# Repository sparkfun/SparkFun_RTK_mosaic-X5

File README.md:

SparkFun RTK mosaic-X5
========================================

[*SparkFun RTK mosaic-X5 (SXM-E)*](https://www.sparkpnt.com/products/sparkpnt-sxm-e-cors)

Designed and manufactured in Boulder, Colorado, USA, the SparkFun RTK mosaic-X5 is the perfect solution for your high-precision positioning and navigation needs. Based around the multi-constellation, multi-frequency, L5-ready mosaic-X5 from Septentrio, this is our most advanced RTK product to date. It supports GNSS signals from GPS (USA), GLONASS (Russia), Beidou (China), Galileo (Europe), Navic (India) plus special additional satellites (e.g. SBAS and QZSS). The mosaic-X5 also has built-in on-module support for other L-band correction services.

The RTK mosaic-X5 can be configured as a Real Time Kinematic (RTK) Base, where it feeds corrections to other RTK Rovers, or as an RTK Rover where it can use corrections to achieve a horizontal positioning accuracy of 6 millimeters (0.6cm) (plus 0.5 PPM). For applications like robotics and autonomous systems, the mosaic-X5 can deliver position updates at 100Hz (100 times per second). The mosaic-X5 is a _very_ sophisticated chip running a full internal web page server; the position can be monitored and the module fully configured through that web page using a standard browser.

Under the hood, the RTK mosaic-X5 is based on the mosaic-X5 GNSS module from Septentrio, plus the Espressif ESP32-WROVER processor (16MB flash, 8MB PSRAM). The mosaic-X5 has USB-C connectivity (with Ethernet-over-USB), multiple UARTs and supports full Ethernet connectivity. The only interface it doesn't offer is WiFi and that's why we've included the ESP32 with its own Ethernet connection. You can connect the mosaic-X5 directly to your Ethernet network - our product supports Power-over-Ethernet too. Or you can link the mosaic-X5 Ethernet port to the ESP32 Ethernet port and have the ESP32 provide WiFi connectivity. In that mode, the ESP32 becomes an Ethernet to WiFi Bridge, seamlessly passing WiFi traffic to and from the mosaic-X5 via Ethernet.

Documentation
--------------

* **[Product Manual](http://docs.sparkfun.com/SparkFun_RTK_mosaic-X5/)** - Product manual for the RTK mosaic-X5 hosted by GitHub pages.<br>

*Need to download or print our hookup guide?*

* [Print *(Print to PDF)* from Single-Page View](http://docs.sparkfun.com/SparkFun_RTK_mosaic-X5/print_view)

Repository Contents
-------------------

* **[/docs](/docs/)** - Online documentation files
    * [assets](/docs/assets/) - Assets files
        * [board_files](/docs/assets/board_files/) - Files for the product design
            * [Schematic](/docs/assets/board_files/schematic.pdf) (.pdf)
            * [Dimensions](/docs/assets/board_files/dimensions.png) (.png)
            * [Eagle files](/docs/assets/board_files/eagle_files.zip) (.zip)
        * [img/hookup_guide/](/docs/assets/img/hookup_guide/) - Images for hookup guide documentation
* **[/Hardware](/Hardware/)** - Eagle design files (.brd, .sch)
* **[/Production](/Production/)** - PCB panel production files
* **[/Extruded_Case](/Extruded_Case/)** - Drawings and STEP file for the extruded case
* **[/Front_Panel](/Front_Panel/)** - Drawings and STEP file. Eagle design files (.brd, .sch) for the prototype (PCB) enclosure panel used to validate the dimensions
* **[/Rear_Panel](/Rear_Panel/)** - Drawings and STEP file. Eagle design files (.brd, .sch) for the prototype (PCB) enclosure panel used to validate the dimensions
* **[/Front_Sticker](/Front_Sticker/)** - DXF and PDF files for the front sticker
* **[/Rear_Sticker](/Rear_Sticker/)** - DXF and PDF files for the rear sticker
* **[/Firmware](/Firmware/)** - ESP IDF source code and binaries for the firmware which runs on the ESP32-WROVER
* **[/Test_Sketches](/Test_Sketches/)** - Additional code used to validate and test the RTK mosaic-X5
* **[/Documents](/Documents/)** - Component datasheets etc.

Product Variants
----------------

* [SXM-E](https://www.sparkpnt.com/products/sparkpnt-sxm-e-cors)- v1.0, Initial Release

Version History
---------------

* [v10](https://github.com/sparkfun/SparkFun_RTK_mosaic-X5/releases/tag/v10) - Initial Release

License Information
-------------------

This product is ***open source***!

Please review the [LICENSE.md](./LICENSE.md) file for license information.

If you have any questions or concerns about licensing, please contact technical support on our [SparkFun forums](https://community.sparkfun.com/).

Distributed as-is; no warranty is given.

- Your friends at SparkFun.

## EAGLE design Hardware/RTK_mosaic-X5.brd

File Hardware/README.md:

SparkFun RTK mosaic-X5 Design Files
=====================================

The .sch and .brd files here are Eagle CAD schematic and PCB design files from SparkFun Electronics.
A freeware version of Autodesk Eagle can be found [here](https://www.autodesk.com/products/eagle/free-download).

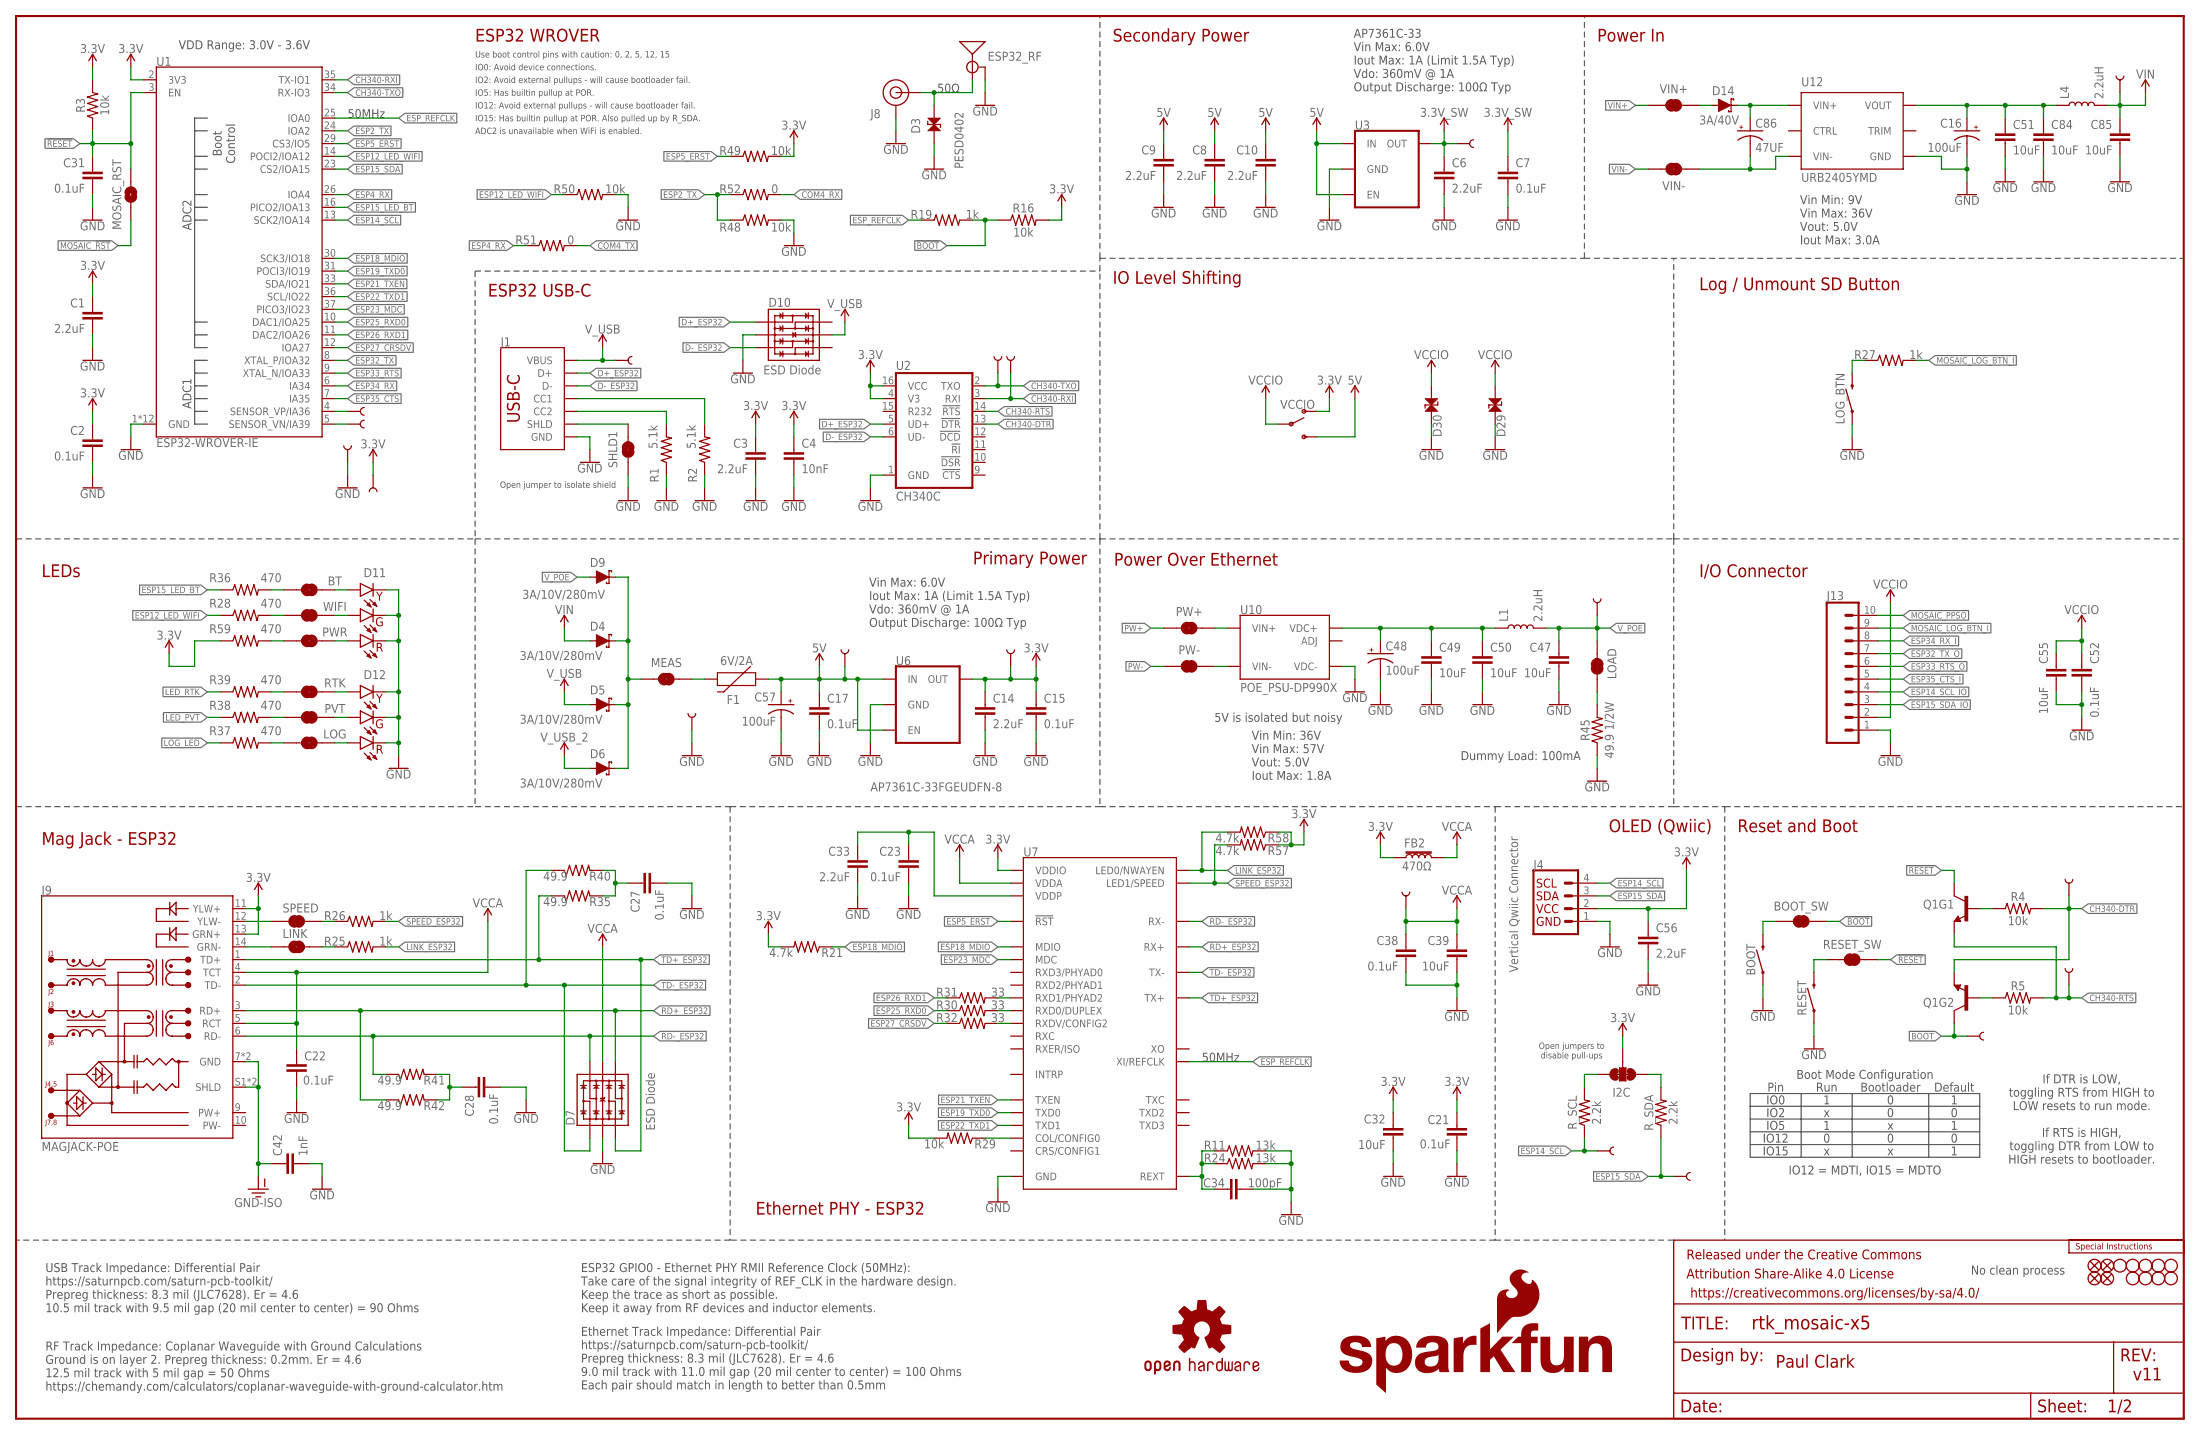
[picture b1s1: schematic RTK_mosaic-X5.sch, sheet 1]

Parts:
3V3, 3V3_SW, 5V: TEST-POINTPOGO_PTH; 1X01_NO_SILK
BOOT: MOMENTARY-SWITCH-SPST-PTH-RIGHT-ANGLE-8-020; TACTILE_SWITCH_PTH_RA_8-020
BOOT_SW: JUMPER-SMT_2_NC_TRACE_SILK; SMT-JUMPER_2_NC_TRACE_SILK
BT: JUMPER-SMT_2_NC_TRACE_SILK; SMT-JUMPER_2_NC_TRACE_SILK
C1, C3, C6, C8, C9, C10, C14, C33, C56: 2.2uF; 0603
C2, C7, C15, C17, C21, C22, C23, C27, C28, C31, C38, C52: 0.1uF; 0603
C4: 10nF; 0603
C16, C48, C57: 100uF; PANASONIC_D
C32, C39, C55: 10uF; 0603
C34: 100pF; 0603
C42: 1nF; 1206
C47, C49, C50, C51, C84, C85: 10uF; 0805
C86: 47UF; PANASONIC_D
D3, D29, D30: PESD0402; 0402
D4, D5, D6, D9: 3A/10V/280mV; SOD-323
D7, D10: ESD Diode; SOT-23-6
D11, D12: Yellow Green Red; CBI_LED_T-3MM_PTH
D14: 3A/40V; SMA-DIODE
DTR: TEST-POINTPOGO_PTH; 1X01_NO_SILK
ESP1, ESP2, ESP36, ESP39: TEST-POINTPOGO_PTH; 1X01_NO_SILK
ESP32_RF: ANTENNA-SMA-GROUNDEDEDGE_RPSMA; RP-SMA-EDGE
F1: 6V/2A; 1210
FB2: 470Ω; 0603
FD1, FD2, FD3, FD4: FIDUCIAL1X2; FIDUCIAL-1X2
FRAME1: FRAME-LEDGER; CREATIVE_COMMONS
GND: TEST-POINTPOGO_PTH; 1X01_NO_SILK
H1, H2, H3, H4, H5, H6, H7, H8, H10: STAND-OFFTIGHT; STAND-OFF-TIGHT
I2C: JUMPER-SMT_3_2-NC_TRACE_SILK; SMT-JUMPER_3_2-NC_TRACE_SILK
J1: USB_C_4-LAYER_PADS; USB-C-16P_4LAYER-PADS
J4: Vertical Qwiic Connector; JST04_1MM_VERT
J8: U.FL2PIN-REDUCED-FOOTPRINT; U.FL_REDUCED_FOOTPRINT
J9: MAGJACK-POE; MAGJACK-SYM_LED
J13: CONN_10_3.5MM_RA_HEADER; 1X10_SCREW_TERMINAL_3.5MM
L1, L4: 2.2uH; 0805-WIDE
LINK: JUMPER-SMT_2_NC_TRACE_SILK; SMT-JUMPER_2_NC_TRACE_SILK
LOAD: JUMPER-SMT_2_NC_TRACE_SILK; SMT-JUMPER_2_NC_TRACE_SILK
LOG: JUMPER-SMT_2_NC_TRACE_SILK; SMT-JUMPER_2_NC_TRACE_SILK
LOGO1: SPECIAL_INSTRUCTIONS-ORDERING; ORDERING_INSTRUCTIONS
LOGO4: OSHW-LOGOS; OSHW-LOGO-S
LOGO5: SFE_LOGO_NAME.2_INCH; SFE_LOGO_NAME_.2
LOGO6: SFE_LOGO_FLAME.2_INCH; SFE_LOGO_FLAME_.2
LOG_BTN: MOMENTARY-SWITCH-SPST-PTH-RIGHT-ANGLE-8-020; TACTILE_SWITCH_PTH_RA_8-020
MEAS: JUMPER-COMBO_2_NC_TRACE; COMBO-JUMPER_2_NC_TRACE
MOSAIC_RST: JUMPER-COMBO_2_NO; COMBO-JUMPER_2_NO
PVT: JUMPER-SMT_2_NC_TRACE_SILK; SMT-JUMPER_2_NC_TRACE_SILK
PW+: JUMPER-COMBO_2_NC_TRACE; COMBO-JUMPER_2_NC_TRACE
PW-: JUMPER-COMBO_2_NC_TRACE; COMBO-JUMPER_2_NC_TRACE
PWR: JUMPER-SMT_2_NC_TRACE_SILK; SMT-JUMPER_2_NC_TRACE_SILK
Q1: TRANS_NPN_DUAL-MBT3904DW1T1; SC70-6
R1, R2: 5.1k; 0603
R3, R4, R5, R16, R29, R48, R49, R50: 10k; 0603
R11, R24: 13k; 0603
R19, R25, R26, R27: 1k; 0603
R21, R57, R58: 4.7k; 0603
R28, R36, R37, R38, R39, R59: 470; 0603
R30, R31, R32: 33; 0603
R35, R40, R41, R42: 49.9; 0603
R45: 49.9 1/2W; 1206
R51, R52: 0; 0603
RESET: MOMENTARY-SWITCH-SPST-PTH-RIGHT-ANGLE-8-020; TACTILE_SWITCH_PTH_RA_8-020
RESET_SW: JUMPER-SMT_2_NC_TRACE_SILK; SMT-JUMPER_2_NC_TRACE_SILK
RTK: JUMPER-SMT_2_NC_TRACE_SILK; SMT-JUMPER_2_NC_TRACE_SILK
RTS: TEST-POINTPOGO_PTH; 1X01_NO_SILK
RX: TEST-POINTPOGO_PTH; 1X01_NO_SILK
R_SCL: 2.2k; 0603
R_SDA: 2.2k; 0603
SCL2: TEST-POINTPOGO_PTH; 1X01_NO_SILK
SDA2: TEST-POINTPOGO_PTH; 1X01_NO_SILK
SHLD1: JUMPER-SMT_2_NC_TRACE_SILK; SMT-JUMPER_2_NC_TRACE_SILK
SPEED: JUMPER-SMT_2_NC_TRACE_SILK; SMT-JUMPER_2_NC_TRACE_SILK
TP_BOOT: TEST-POINTPOGO_PTH; 1X01_NO_SILK
TX: TEST-POINTPOGO_PTH; 1X01_NO_SILK
U1: ESP32-WROVER-IE; ESP32-WROVER-E/IE
U2: CH340C; SO016
U3, U6: AP7361C-33FGEUDFN-8; UDFN-8
U7: KSZ8041NLI; MLF55Q-32LD
U10: POE_PSU-DP990X; DP990X
U12: URB2405YMD; URB_YMD-15WR3
VCCA: TEST-POINTPOGO_PTH; 1X01_NO_SILK
VCCIO: SWITCH-SPDT-SMD-AYZ0202; SWITCH_DPDT_SMD_AYZ0202
VIN: TEST-POINTPOGO_PTH; 1X01_NO_SILK
VIN+: JUMPER-COMBO_2_NC_TRACE; COMBO-JUMPER_2_NC_TRACE
VIN-: JUMPER-COMBO_2_NC_TRACE; COMBO-JUMPER_2_NC_TRACE
VPOE: TEST-POINTPOGO_PTH; 1X01_NO_SILK
VUSB: TEST-POINTPOGO_PTH; 1X01_NO_SILK
WIFI: JUMPER-SMT_2_NC_TRACE_SILK; SMT-JUMPER_2_NC_TRACE_SILK

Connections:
3.3V: 3V3.1, C1.1, C2.1, C3.1, C4.1, C14.1, C15.1, C21.1, C32.1, C56.1, ESP2.1, FB2.1, I2C.2, J4.2, J9.11 (YLW+), J9.13 (GRN+), R3.2, R16.2, R21.2, R29.2, R49.2, R57.1, R58.1, R59.1, U1.2 (3V3), U2.4 (V3), U2.16 (VCC), U6.1 (OUT), U7.17 (VDDIO), VCCIO.1 (O); also elsewhere on the board
3.3V_SW: 3V3_SW.1, C6.1, C7.1, U3.1 (OUT); also elsewhere on the board
5V: 5V.1, C8.1, C9.1, C10.1, C17.1, C57.+, F1.1, U3.5 (EN), U3.8 (IN), U6.5 (EN), U6.8 (IN), VCCIO.3 (S); also elsewhere on the board
5V_RAW: C48.+, C49.1, C50.1, L1.1, U10.1 (VDC+), U10.2 (VDC+)
5V_RAW1: C16.+, C51.1, C84.1, L4.1, U12.4 (VOUT)
!BOOT!: BOOT_SW.1, Q1.6 (C), R16.1, R19.2, TP_BOOT.1
!RESET!: C31.1, MOSAIC_RST.2, MOSAIC_RST.4 (2), Q1.3 (C), R3.1, RESET_SW.1, U1.3 (EN)
CH340-DTR: DTR.1, Q1.1 (E), R4.2, U2.13 (!DTR)
CH340-RTS: Q1.4 (E), R5.2, RTS.1, U2.14 (!RTS)
CH340-RXI: TX.1, U1.35 (TX-IO1), U2.3 (RXI)
CH340-TXO: RX.1, U1.34 (RX-IO3), U2.2 (TXO)
COM4_RX: R52.2; also elsewhere on the board
COM4_TX: R51.2; also elsewhere on the board
D+_ESP32: D10.1 (IO1), J1.A6 (D+), J1.B6 (D+), U2.5 (UD+)
D-_ESP32: D10.3 (IO2), J1.A7 (D-), J1.B7 (D-), U2.6 (UD-)
ESP2_TX: R48.1, R52.1, U1.24 (IOA2)
ESP4_RX: R51.1, U1.26 (IOA4)
ESP5_ERST: R49.1, U1.29 (CS3/IO5), U7.32 (!RST!)
ESP12_LED_WIFI: R28.1, R50.1, U1.14 (POCI2/IOA12)
ESP14_SCL: J4.4, R_SCL.1, SCL2.1, U1.13 (SCK2/IOA14); also elsewhere on the board
ESP14_SCL_IO: J13.4; also elsewhere on the board
ESP15_LED_BT: R36.1, U1.16 (PICO2/IOA13)
ESP15_SDA: J4.3, R_SDA.1, SDA2.1, U1.23 (CS2/IOA15); also elsewhere on the board
ESP15_SDA_IO: J13.3; also elsewhere on the board
ESP18_MDIO: R21.1, U1.30 (SCK3/IO18), U7.11 (MDIO)
ESP19_TXD0: U1.31 (POCI3/IO19), U7.24 (TXD0)
ESP21_TXEN: U1.33 (SDA/IO21), U7.23 (TXEN)
ESP22_TXD1: U1.36 (SCL/IO22), U7.25 (TXD1)
ESP23_MDC: U1.37 (PICO3/IO23), U7.12 (MDC)
ESP25_RXD0: R30.1, U1.10 (DAC1/IOA25)
ESP26_RXD1: R31.1, U1.11 (DAC2/IOA26)
ESP27_CRSDV: R32.1, U1.12 (IOA27)
ESP32_RF: D3.1, ESP32_RF.SIG (SIGNAL), J8.FEED (SIGNAL)
ESP32_TX: U1.8 (XTAL_P/IOA32); also elsewhere on the board
ESP32_TX_O: J13.7; also elsewhere on the board
ESP33_RTS: U1.9 (XTAL_N/IOA33); also elsewhere on the board
ESP33_RTS_O: J13.6; also elsewhere on the board
ESP34_RX: U1.6 (IA34); also elsewhere on the board
ESP34_RX_I: J13.8; also elsewhere on the board
ESP35_CTS: U1.7 (IA35); also elsewhere on the board
ESP35_CTS_I: J13.5; also elsewhere on the board
ESP36: ESP36.1, U1.4 (SENSOR_VP/IA36)
ESP39: ESP39.1, U1.5 (SENSOR_VN/IA39)
ESP_REFCLK: R19.1, U1.25 (IOA0), U7.9 (XI/REFCLK)
GND: BOOT.1, C1.2, C2.2, C3.2, C4.2, C6.2, C7.2, C8.2, C9.2, C10.2, C14.2, C15.2, C16.-, C17.2, C21.2, C22.2, C23.2, C27.2, C28.2, C31.2, C32.2, C33.2, C34.2, C38.2, C39.2, C42.2, C47.2, C48.-, C49.2, C50.2, C51.2, C52.2, C55.2, C56.2, C57.-, C84.2, C85.2, D3.2, D7.2 (VSS), D10.2 (VSS), D11.CATHODE_1 (YELLOW_CATHODE), D11.CATHODE_2 (GREEN_CATHODE), D11.CATHODE_3 (RED_CATHODE), D12.CATHODE_1 (YELLOW_CATHODE), D12.CATHODE_2 (GREEN_CATHODE), D12.CATHODE_3 (RED_CATHODE), D29.2, D30.2, ESP1.1, ESP32_RF.GND@0 (GND), ESP32_RF.GND@1 (GND), ESP32_RF.GND@2 (GND), ESP32_RF.GND@3 (GND), GND.1, J1.GND, J1.GND2 (GND), J4.1, J8.1 (GND), J8.2 (GND), J13.1, LOG_BTN.1, R1.1, R2.1, R11.2, R24.2, R45.1, R48.2, R50.2, RESET.1, SHLD1.1, U1.1 (GND), U1.15 (GND), U1.38 (GND), U1.GND, U1.GNDT1 (GND), U1.GNDT2 (GND), U1.GNDT3 (GND), U1.GNDT4 (GND), U1.GNDT5 (GND), U1.GNDT6 (GND), U1.GNDT7 (GND), U1.GNDT8 (GND), U2.1 (GND), U3.4 (GND), U3.EP (GND), U6.4 (GND), U6.EP (GND), U7.1 (GND), U7.GND, U10.3 (VDC-), U12.6 (GND); also elsewhere on the board
GND-ISO: C42.1, J9.7 (GND), J9.8 (GND), J9.S1 (SHLD), J9.S2 (SHLD); also elsewhere on the board
LED_PVT: R38.1; also elsewhere on the board
LED_RTK: R39.1; also elsewhere on the board
LINK_ESP32: R25.2, R58.2, U7.30 (LED0/NWAYEN)
LOG_LED: R37.1; also elsewhere on the board
MEAS: D4.C, D5.C, D6.C, D9.C, MEAS.2, MEAS.4 (2)
MOSAIC_!RST!: MOSAIC_RST.1, MOSAIC_RST.3 (1); also elsewhere on the board
MOSAIC_LOG_BTN_I: J13.9, R27.2; also elsewhere on the board
MOSAIC_PPSO: J13.10; also elsewhere on the board
unnamed: J1.B5 (CC2), R1.2
unnamed: J1.A5 (CC1), R2.2
unnamed: J9.14 (GRN-), LINK.1
unnamed: Q1.2 (B), R5.1
unnamed: Q1.5 (B), R4.1
unnamed: J9.12 (YLW-), SPEED.1
unnamed: F1.2, MEAS.1, MEAS.3 (1)
unnamed: LOG_BTN.2, R27.1
unnamed: R26.1, SPEED.2
unnamed: I2C.3, R_SCL.2
unnamed: I2C.1, R_SDA.2
unnamed: LOG.2, R37.2
unnamed: D12.ANODE_3 (RED_ANODE), LOG.1
unnamed: D11.ANODE_2 (GREEN_ANODE), WIFI.1
unnamed: C27.1, R35.2, R40.2
unnamed: C28.1, R41.2, R42.2
unnamed: LINK.2, R25.1
unnamed: BT.1, D11.ANODE_1 (YELLOW_ANODE)
unnamed: C23.1, C33.1, U7.2 (VDDP)
unnamed: C34.1, R11.1, R24.1, U7.10 (REXT)
unnamed: R29.1, U7.28 (COL/CONFIG0)
unnamed: BT.2, R36.2
unnamed: LOAD.1, R45.2
unnamed: RESET.2, RESET_SW.2
unnamed: BOOT.2, BOOT_SW.2
unnamed: R30.2, U7.16 (RXD0/DUPLEX)
unnamed: R31.2, U7.15 (RXD1/PHYAD2)
unnamed: R28.2, WIFI.2
unnamed: D12.ANODE_2 (GREEN_ANODE), PVT.1
unnamed: D12.ANODE_1 (YELLOW_ANODE), RTK.1
unnamed: R39.2, RTK.2
unnamed: PVT.2, R38.2
unnamed: R32.2, U7.18 (RXDV/CONFIG2)
unnamed: PWR.2, R59.2
unnamed: D11.ANODE_3 (RED_ANODE), PWR.1
PW1+: PW+.1, PW+.3 (1), U10.5 (VIN+), U10.6 (VIN+)
PW1-: PW-.1, PW-.3 (1), U10.7 (VIN-), U10.8 (VIN-)
PW+: PW+.2, PW+.4 (2); also elsewhere on the board
PW-: PW-.2, PW-.4 (2); also elsewhere on the board
RD+_ESP32: D7.4 (IO3), J9.3 (RD+), R42.1, U7.5 (RX+)
RD-_ESP32: D7.6 (IO4), J9.6 (RD-), R41.1, U7.4 (RX-)
SHIELD: J1.SHLD1 (SHLD), J1.SHLD2 (SHLD), J1.SHLD3 (SHLD), J1.SHLD4 (SHLD), SHLD1.2
SPEED_ESP32: R26.2, R57.2, U7.31 (LED1/SPEED)
TD+_ESP32: D7.3 (IO2), J9.1 (TD+), R35.1, U7.7 (TX+)
TD-_ESP32: D7.1 (IO1), J9.2 (TD-), R40.1, U7.6 (TX-)
VCCA: C22.1, C38.1, C39.1, D7.5 (VCC), FB2.2, J9.4 (TCT), J9.5 (RCT), U7.3 (VDDA), VCCA.1
VCCIO: C52.1, C55.1, D29.1, D30.1, J13.2, VCCIO.2; also elsewhere on the board
VIN: C85.1, D4.A, L4.2, VIN.1
VIN1+: D14.A, VIN+.1, VIN+.3 (1)
VIN1-: C86.-, U12.2 (VIN-), VIN-.2, VIN-.4 (2)
VIN2+: C86.+, D14.C, U12.3 (VIN+)
VIN+: VIN+.2, VIN+.4 (2); also elsewhere on the board
VIN-: VIN-.1, VIN-.3 (1); also elsewhere on the board
V_POE: C47.1, D9.A, L1.2, LOAD.2, VPOE.1
V_USB: D5.A, D10.5 (VCC), J1.VBUS1 (VBUS), J1.VBUS2 (VBUS), VUSB.1
V_USB_2: D6.A; also elsewhere on the board

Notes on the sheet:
ESP32 WROVER
ESP32 USB-C
Paul Clark
v11
Reset and Boot
Secondary Power
Primary Power
Ethernet PHY - ESP32
Mag Jack - ESP32
VDD Range: 3.0V - 3.6V
If DTR is LOW, toggling RTS from HIGH to LOW resets to run mode. If RTS is HIGH, toggling DTR from LOW to HIGH resets to bootloader.
Pin
IO0
IO2
IO12
IO15
IO5
Run
Bootloader
Default
IO12 = MDTI, IO15 = MDTO
Boot Mode Configuration
IO0: Avoid device connections.
ADC2 is unavailable when WiFi is enabled.
IO12: Avoid external pullups - will cause bootloader fail.
Use boot control pins with caution: 0, 2, 5, 12, 15
IO2: Avoid external pullups - will cause bootloader fail.
IO15: Has builtin pullup at POR. Also pulled up by R_SDA.
IO5: Has builtin pullup at POR.
Open jumpers to disable pull-ups
Open jumper to isolate shield
AP7361C-33 Vin Max: 6.0V Iout Max: 1A (Limit 1.5A Typ) Vdo: 360mV @ 1A Output Discharge: 100Ω Typ
RF Track Impedance: Coplanar Waveguide with Ground Calculations Ground is on layer 2. Prepreg thickness: 0.2mm. Er = 4.6 12.5 mil track with 5 mil gap = 50 Ohms https://chemandy.com/calculators/coplanar-waveguide-with-ground-calculator.htm
USB Track Impedance: Differential Pair https://saturnpcb.com/saturn-pcb-toolkit/ Prepreg thickness: 8.3 mil (JLC7628). Er = 4.6 10.5 mil track with 9.5 mil gap (20 mil center to center) = 90 Ohms
50Ω
Power Over Ethernet
5V is isolated but noisy
Dummy Load: 100mA
Power In
OLED (Qwiic)

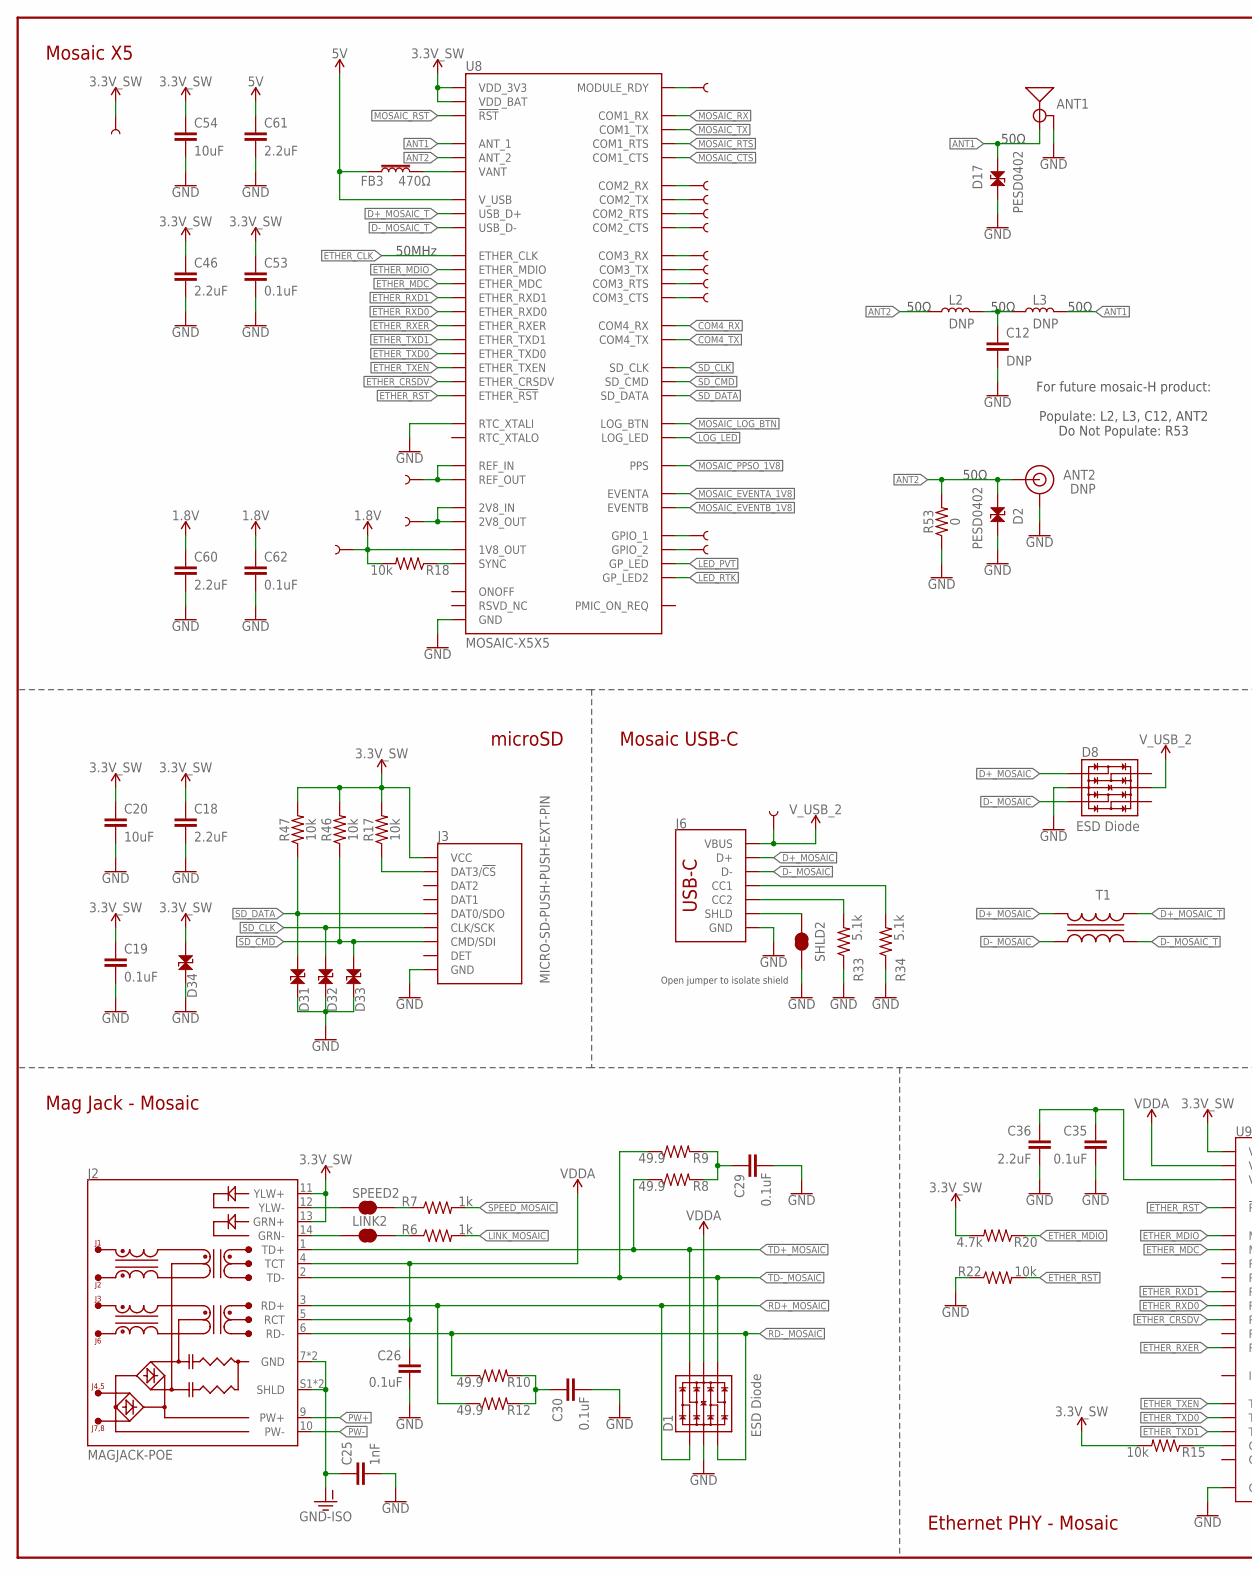
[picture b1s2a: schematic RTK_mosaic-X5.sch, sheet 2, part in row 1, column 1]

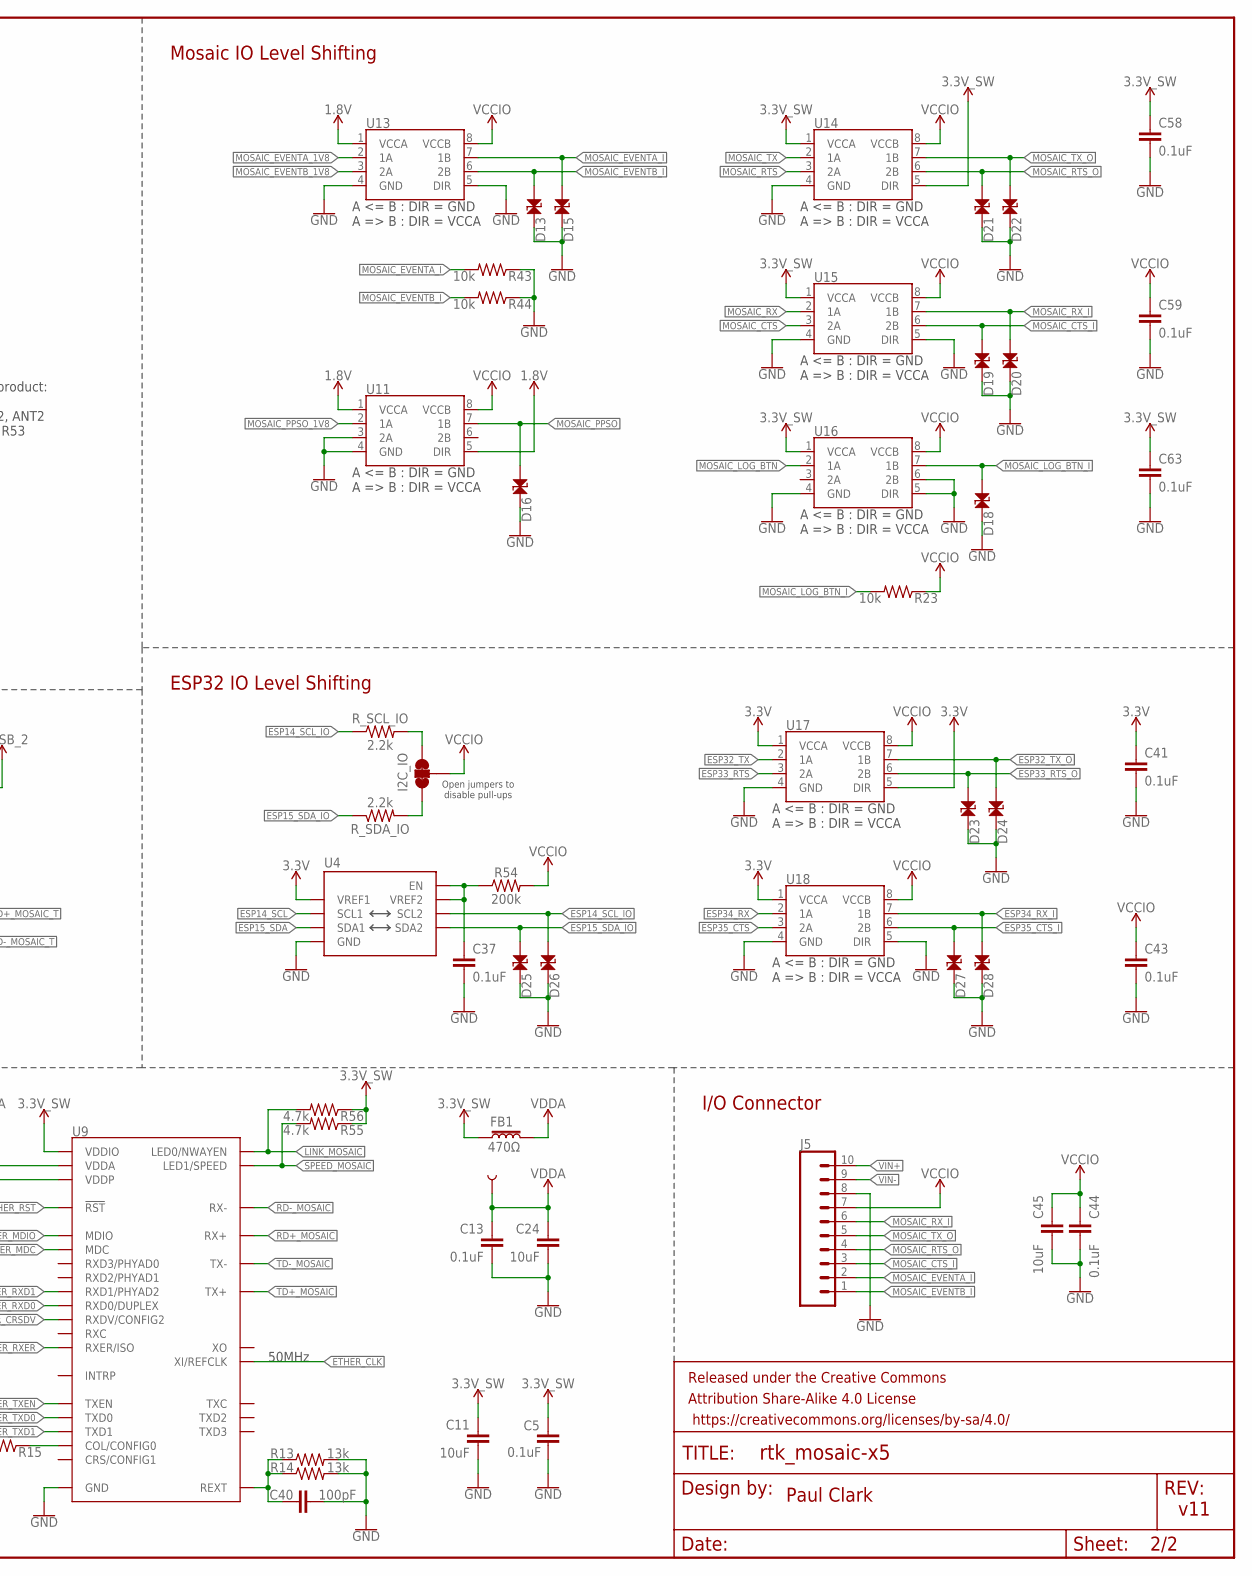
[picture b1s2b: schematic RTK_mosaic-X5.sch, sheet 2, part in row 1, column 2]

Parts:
1V8, 2V8: TEST-POINTPOGO_PTH; 1X01_NO_SILK
ANT1: ANTENNA-SMA-GROUNDEDEDGE_SMA; SMA-EDGE
ANT2: DNP; U.FL_REDUCED_FOOTPRINT__NO_CREAM
C5, C13, C19, C26, C29, C30, C35, C37, C41, C43, C44, C53, C58, C59, C62, C63: 0.1uF; 0603
C11, C20, C24, C45, C54: 10uF; 0603
C12: DNP; 0603_NO_CREAM
C18, C36, C46, C60, C61: 2.2uF; 0603
C25: 1nF; 1206
C40: 100pF; 0603
COM2_CTS, COM2_RTS, COM2_RX, COM2_TX, COM3_CTS, COM3_RTS, COM3_RX, COM3_TX: TEST-POINTPOGO_PTH; 1X01_NO_SILK
D1, D8: ESD Diode; SOT-23-6
D2, D13, D15, D16, D17, D18, D19, D20, D21, D22, D23, D24, D25, D26, D27, D28, D31, D32, D33, D34: PESD0402; 0402
FB1, FB3: 470Ω; 0603
FRAME3: FRAME-LEDGERNO_FOOTPRINT; DUMMY
GPIO_1, GPIO_2: TEST-POINTPOGO_PTH; 1X01_NO_SILK
I2C_IO: JUMPER-SMT_3_2-NC_TRACE_SILK; SMT-JUMPER_3_2-NC_TRACE_SILK
J2: MAGJACK-POE; MAGJACK-SYM_LED
J3: MICRO-SD-PUSH-PUSH-EXT-PIN; MICROSD-EXTERNALPIN
J5: CONN_10_3.5MM_RA_HEADER; 1X10_SCREW_TERMINAL_3.5MM
J6: USB_C_4-LAYER_PADS; USB-C-16P_4LAYER-PADS
L2, L3: DNP; 0603_NO-CREAM
LINK2: JUMPER-SMT_2_NC_TRACE_SILK; SMT-JUMPER_2_NC_TRACE_SILK
R6, R7: 1k; 0603
R8, R9, R10, R12: 49.9; 0603
R13, R14: 13k; 0603
R15, R17, R18, R22, R23, R43, R44, R46, R47: 10k; 0603
R20, R55, R56: 4.7k; 0603
R33, R34: 5.1k; 0603
R53: 0; 0603
R54: 200k; 0603
RDY, RDY1: TEST-POINTPOGO_PTH; 1X01_NO_SILK
REF: TEST-POINTPOGO_PTH; 1X01_NO_SILK
R_SCL_IO: 2.2k; 0603
R_SDA_IO: 2.2k; 0603
SHLD2: JUMPER-SMT_2_NC_TRACE_SILK; SMT-JUMPER_2_NC_TRACE_SILK
SPEED2: JUMPER-SMT_2_NC_TRACE_SILK; SMT-JUMPER_2_NC_TRACE_SILK
T1: TRANSFORMER0508; RFCMF1220100M4T
U4: PCA9306VSSOP_8PIN; VSSOP_8PIN
U8: MOSAIC-X5X5; MOSAIC_LGA
U9: KSZ8041NLI; MLF55Q-32LD
U11, U13, U14, U15, U16, U17, U18: 74LVC2T45DC; VSSOP8_(SOT765-1)
VDDA: TEST-POINTPOGO_PTH; 1X01_NO_SILK
VUSB2: TEST-POINTPOGO_PTH; 1X01_NO_SILK

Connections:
1.8V: 1V8.1, C60.1, C62.1, R18.2, U8.AC4 (1V8_OUT), U11.1 (VCCA), U11.5 (DIR), U13.1 (VCCA)
2V8: 2V8.1, U8.M23 (2V8_IN), U8.N23 (2V8_OUT)
3.3V: C41.1, U4.P2 (VREF1), U17.1 (VCCA), U17.5 (DIR), U18.1 (VCCA); also elsewhere on the board
3.3V_SW: C5.1, C11.1, C18.1, C19.1, C20.1, C46.1, C53.1, C54.1, C58.1, C63.1, D34.1, FB1.1, J2.11 (YLW+), J2.13 (GRN+), J3.4 (VCC), R15.2, R17.2, R20.2, R46.2, R47.2, R55.1, R56.1, RDY1.1, U8.A18 (VDD_3V3), U8.A19 (VDD_3V3), U8.A20 (VDD_3V3), U8.B8 (VDD_BAT), U8.B18 (VDD_3V3), U8.B19 (VDD_3V3), U8.B20 (VDD_3V3), U8.C18 (VDD_3V3), U8.C19 (VDD_3V3), U8.C20 (VDD_3V3), U9.17 (VDDIO), U14.1 (VCCA), U14.5 (DIR), U15.1 (VCCA), U16.1 (VCCA); also elsewhere on the board
5V: C61.1, FB3.1, U8.A8 (V_USB); also elsewhere on the board
ANT1: ANT1.SIG (SIGNAL), D17.1, L3.2, U8.AC20 (ANT_1)
ANT2: ANT2.FEED (SIGNAL), D2.1, L2.1, R53.2, U8.V23 (ANT_2)
COM2_CTS: COM2_CTS.1, U8.J1 (COM2_CTS)
COM2_RTS: COM2_RTS.1, U8.G1 (COM2_RTS)
COM2_RX: COM2_RX.1, U8.F1 (COM2_RX)
COM2_TX: COM2_TX.1, U8.H1 (COM2_TX)
COM3_CTS: COM3_CTS.1, U8.N1 (COM3_CTS)
COM3_RTS: COM3_RTS.1, U8.L1 (COM3_RTS)
COM3_RX: COM3_RX.1, U8.K1 (COM3_RX)
COM3_TX: COM3_TX.1, U8.M1 (COM3_TX)
COM4_RX: U8.D3 (COM4_RX); also elsewhere on the board
COM4_TX: U8.E3 (COM4_TX); also elsewhere on the board
D+_MOSAIC: D8.1 (IO1), J6.A6 (D+), J6.B6 (D+), T1.A2
D+_MOSAIC_T: T1.A1, U8.A5 (USB_D+)
D-_MOSAIC: D8.3 (IO2), J6.A7 (D-), J6.B7 (D-), T1.B2
D-_MOSAIC_T: T1.B1, U8.A6 (USB_D-)
ESP14_SCL: U4.P3 (SCL1); also elsewhere on the board
ESP14_SCL_IO: D26.1, R_SCL_IO.1, U4.P6 (SCL2); also elsewhere on the board
ESP15_SDA: U4.P4 (SDA1); also elsewhere on the board
ESP15_SDA_IO: D25.1, R_SDA_IO.1, U4.P5 (SDA2); also elsewhere on the board
ESP32_TX: U17.2 (1A); also elsewhere on the board
ESP32_TX_O: D24.1, U17.7 (1B); also elsewhere on the board
ESP33_RTS: U17.3 (2A); also elsewhere on the board
ESP33_RTS_O: D23.1, U17.6 (2B); also elsewhere on the board
ESP34_RX: U18.2 (1A); also elsewhere on the board
ESP34_RX_I: D28.1, U18.7 (1B); also elsewhere on the board
ESP35_CTS: U18.3 (2A); also elsewhere on the board
ESP35_CTS_I: D27.1, U18.6 (2B); also elsewhere on the board
ETHER_!RST!: R22.2, U8.F2 (ETHER_!RST!), U9.32 (!RST!)
ETHER_CLK: U8.AA2 (ETHER_CLK), U9.9 (XI/REFCLK)
ETHER_CRSDV: U8.N2 (ETHER_CRSDV), U9.18 (RXDV/CONFIG2)
ETHER_MDC: U8.V2 (ETHER_MDC), U9.12 (MDC)
ETHER_MDIO: R20.1, U8.W2 (ETHER_MDIO), U9.11 (MDIO)
ETHER_RXD0: U8.R2 (ETHER_RXD0), U9.16 (RXD0/DUPLEX)
ETHER_RXD1: U8.T2 (ETHER_RXD1), U9.15 (RXD1/PHYAD2)
ETHER_RXER: U8.M2 (ETHER_RXER), U9.20 (RXER/ISO)
ETHER_TXD0: U8.J2 (ETHER_TXD0), U9.24 (TXD0)
ETHER_TXD1: U8.H2 (ETHER_TXD1), U9.25 (TXD1)
ETHER_TXEN: U8.L2 (ETHER_TXEN), U9.23 (TXEN)
GND: ANT1.GND@0 (GND), ANT1.GND@1 (GND), ANT1.GND@2 (GND), ANT1.GND@3 (GND), ANT2.1 (GND), ANT2.2 (GND), C5.2, C11.2, C12.2, C13.2, C18.2, C19.2, C20.2, C24.2, C25.2, C26.2, C29.2, C30.2, C35.2, C36.2, C37.2, C40.2, C41.2, C43.2, C44.2, C45.2, C46.2, C53.2, C54.2, C58.2, C59.2, C60.2, C61.2, C62.2, C63.2, D1.2 (VSS), D2.2, D8.2 (VSS), D13.2, D15.2, D16.2, D17.2, D18.2, D19.2, D20.2, D21.2, D22.2, D23.2, D24.2, D25.2, D26.2, D27.2, D28.2, D31.2, D32.2, D33.2, D34.2, J3.6 (GND), J3.10 (GND), J3.11 (GND), J3.12 (GND), J3.13 (GND), J5.8, J6.GND, J6.GND2 (GND), R13.2, R14.2, R22.1, R33.1, R34.1, R43.1, R44.1, R53.1, SHLD2.1, U4.P1 (GND), U8.A3 (RTC_XTALI), U8.A4 (GND), U8.A7 (GND), U8.A15 (GND), U8.A16 (GND), U8.A17 (GND), U8.A21 (GND), U8.A22 (GND), U8.A23 (GND), U8.AA13 (GND), U8.AA14 (GND), U8.AA15 (GND), U8.AA16 (GND), U8.AA17 (GND), U8.AA18 (GND), U8.AA19 (GND), U8.AA20 (GND), U8.AA21 (GND), U8.AA22 (GND), U8.AA23 (GND), U8.AB2 (GND), U8.AB3 (GND), U8.AB4 (GND), U8.AB5 (GND), U8.AB6 (GND), U8.AB7 (GND), U8.AB8 (GND), U8.AB13 (GND), U8.AB14 (GND), U8.AB15 (GND), U8.AB16 (GND), U8.AB17 (GND), U8.AB18 (GND), U8.AB19 (GND), U8.AB20 (GND), U8.AB21 (GND), U8.AB22 (GND), U8.AB23 (GND), U8.AC13 (GND), U8.AC15 (GND), U8.AC18 (GND), U8.AC19 (GND), U8.AC21 (GND), U8.AC22 (GND), U8.AC23 (GND), U8.B4 (GND), U8.B5 (GND), U8.B6 (GND), U8.B7 (GND), U8.B13 (GND), U8.B17 (GND), U8.B21 (GND), U8.C4 (GND), U8.C7 (GND), U8.C15 (GND), U8.C16 (GND), U8.C17 (GND), U8.C23 (GND), U8.D2 (GND), U8.D21 (GND), U8.D22 (GND), U8.D23 (GND), U8.E2 (GND), U8.E21 (GND), U8.E22 (GND), U8.E23 (GND), U8.F21 (GND), U8.F22 (GND), U8.F23 (GND), U8.G2 (GND), U8.G21 (GND), U8.G23 (GND), U8.H21 (GND), U8.H22 (GND), U8.H23 (GND), U8.J21 (GND), U8.J22 (GND), U8.J23 (GND), U8.K2 (GND), U8.K21 (GND), U8.K22 (GND), U8.K23 (GND), U8.L21 (GND), U8.L22 (GND), U8.L23 (GND), U8.M21 (GND), U8.M22 (GND), U8.N21 (GND), U8.N22 (GND), U8.P1 (GND), U8.P2 (GND), U8.P3 (GND), U8.P21 (GND), U8.P22 (GND), U8.R3 (GND), U8.R21 (GND), U8.R22 (GND), U8.T21 (GND), U8.T22 (GND), U8.T23 (GND), U8.U2 (GND), U8.U21 (GND), U8.U22 (GND), U8.U23 (GND), U8.V21 (GND), U8.V22 (GND), U8.W21 (GND), U8.W22 (GND), U8.W23 (GND), U8.Y2 (GND), U8.Y21 (GND), U8.Y22 (GND), U8.Y23 (GND), U9.1 (GND), U9.GND, U11.3 (2A), U11.4 (GND), U13.4 (GND), U13.5 (DIR), U14.4 (GND), U15.4 (GND), U15.5 (DIR), U16.4 (GND), U16.5 (DIR), U16.6 (2B), U17.4 (GND), U18.4 (GND), U18.5 (DIR); also elsewhere on the board
GND-ISO: C25.1, J2.7 (GND), J2.8 (GND), J2.S1 (SHLD), J2.S2 (SHLD); also elsewhere on the board
GPIO_1: GPIO_1.1, U8.AA4 (GPIO_1)
GPIO_2: GPIO_2.1, U8.L3 (GPIO_2)
LED_PVT: U8.A14 (GP_LED); also elsewhere on the board
LED_RTK: U8.M3 (GP_LED2); also elsewhere on the board
LINK_MOSAIC: R6.2, R56.2, U9.30 (LED0/NWAYEN)
LOG_LED: U8.B2 (LOG_LED); also elsewhere on the board
MOSAIC_!RST!: U8.A11 (!RST!); also elsewhere on the board
MOSAIC_CTS: U8.E1 (COM1_CTS), U15.3 (2A)
MOSAIC_CTS_I: D19.1, J5.3, U15.6 (2B)
MOSAIC_EVENTA_1V8: U8.AC6 (EVENTA), U13.2 (1A)
MOSAIC_EVENTA_I: D15.1, J5.2, R43.2, U13.7 (1B)
MOSAIC_EVENTB_1V8: U8.AC7 (EVENTB), U13.3 (2A)
MOSAIC_EVENTB_I: D13.1, J5.1, R44.2, U13.6 (2B)
MOSAIC_LOG_BTN: U8.K3 (LOG_BTN), U16.2 (1A)
MOSAIC_LOG_BTN_I: D18.1, R23.2, U16.7 (1B); also elsewhere on the board
MOSAIC_PPSO: D16.1, U11.7 (1B); also elsewhere on the board
MOSAIC_PPSO_1V8: U8.AC8 (PPS), U11.2 (1A)
MOSAIC_RTS: U8.C1 (COM1_RTS), U14.3 (2A)
MOSAIC_RTS_O: D21.1, J5.4, U14.6 (2B)
MOSAIC_RX: U8.B1 (COM1_RX), U15.2 (1A)
MOSAIC_RX_I: D20.1, J5.6, U15.7 (1B)
MOSAIC_TX: U8.D1 (COM1_TX), U14.2 (1A)
MOSAIC_TX_O: D22.1, J5.5, U14.7 (1B)
unnamed: C37.1, R54.1, U4.P7 (VREF2), U4.P8 (EN)
unnamed: J6.SHLD1 (SHLD), J6.SHLD2 (SHLD), J6.SHLD3 (SHLD), J6.SHLD4 (SHLD), SHLD2.2
unnamed: R18.1, U8.AC3 (SYNC)
unnamed: C12.1, L2.2, L3.1
unnamed: J6.B5 (CC2), R33.2
unnamed: J6.A5 (CC1), R34.2
unnamed: J2.14 (GRN-), LINK2.1
unnamed: J2.12 (YLW-), SPEED2.1
unnamed: I2C_IO.3, R_SCL_IO.2
unnamed: I2C_IO.1, R_SDA_IO.2
unnamed: R7.1, SPEED2.2
unnamed: LINK2.2, R6.1
unnamed: C29.1, R8.2, R9.2
unnamed: C30.1, R10.2, R12.2
unnamed: C35.1, C36.1, U9.2 (VDDP)
unnamed: C40.1, R13.1, R14.1, U9.10 (REXT)
unnamed: R15.1, U9.28 (COL/CONFIG0)
PW+: J2.9 (PW+); also elsewhere on the board
PW-: J2.10 (PW-); also elsewhere on the board
RD+_MOSAIC: D1.1 (IO1), J2.3 (RD+), R12.1, U9.5 (RX+)
RD-_MOSAIC: D1.3 (IO2), J2.6 (RD-), R10.1, U9.4 (RX-)
RDY: RDY.1, U8.A12 (MODULE_RDY)
REF: REF.1, U8.AC16 (REF_OUT), U8.AC17 (REF_IN)
SD_CLK: D32.1, J3.5 (CLK/SCK), U8.AA1 (SD_CLK)
SD_CMD: D33.1, J3.3 (CMD/SDI), R46.1, U8.AB1 (SD_CMD)
SD_DAT3: J3.2 (DAT3/!CS!), R17.1
SD_DATA: D31.1, J3.7 (DAT0/SDO), R47.1, U8.Y1 (SD_DATA)
SPEED_MOSAIC: R7.2, R55.2, U9.31 (LED1/SPEED)
TD+_MOSAIC: D1.6 (IO4), J2.1 (TD+), R8.1, U9.7 (TX+)
TD-_MOSAIC: D1.4 (IO3), J2.2 (TD-), R9.1, U9.6 (TX-)
VANT: FB3.2, U8.P23 (VANT), U8.R23 (VANT)
VCCIO: C43.1, C44.1, C45.1, C59.1, I2C_IO.2, J5.7, R23.1, R54.2, U11.8 (VCCB), U13.8 (VCCB), U14.8 (VCCB), U15.8 (VCCB), U16.8 (VCCB), U17.8 (VCCB), U18.8 (VCCB); also elsewhere on the board
VDDA: C13.1, C24.1, C26.1, D1.5 (VCC), FB1.2, J2.4 (TCT), J2.5 (RCT), U9.3 (VDDA), VDDA.1
VIN+: J5.10; also elsewhere on the board
VIN-: J5.9; also elsewhere on the board
V_USB_2: D8.5 (VCC), J6.VBUS1 (VBUS), J6.VBUS2 (VBUS), VUSB2.1; also elsewhere on the board

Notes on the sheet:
microSD
Mosaic USB-C
Open jumper to isolate shield
Ethernet PHY - Mosaic
Mag Jack - Mosaic
I/O Connector
Mosaic X5
Mosaic IO Level Shifting
50Ω
Paul Clark
v11
For future mosaic-H product: Populate: L2, L3, C12, ANT2 Do Not Populate: R53
Open jumpers to disable pull-ups
ESP32 IO Level Shifting
50MHz

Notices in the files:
parts and their libraries:
SparkFun-Capacitors: Licensing: Creative Commons ShareAlike 4.0 International - https://creativecommons.org/licenses/by-sa/4.0
SparkFun-Aesthetics: Released under the Creative Commons Attribution Share-Alike 4.0 License
SparkFun-Aesthetics: https://creativecommons.org/licenses/by-sa/4.0
